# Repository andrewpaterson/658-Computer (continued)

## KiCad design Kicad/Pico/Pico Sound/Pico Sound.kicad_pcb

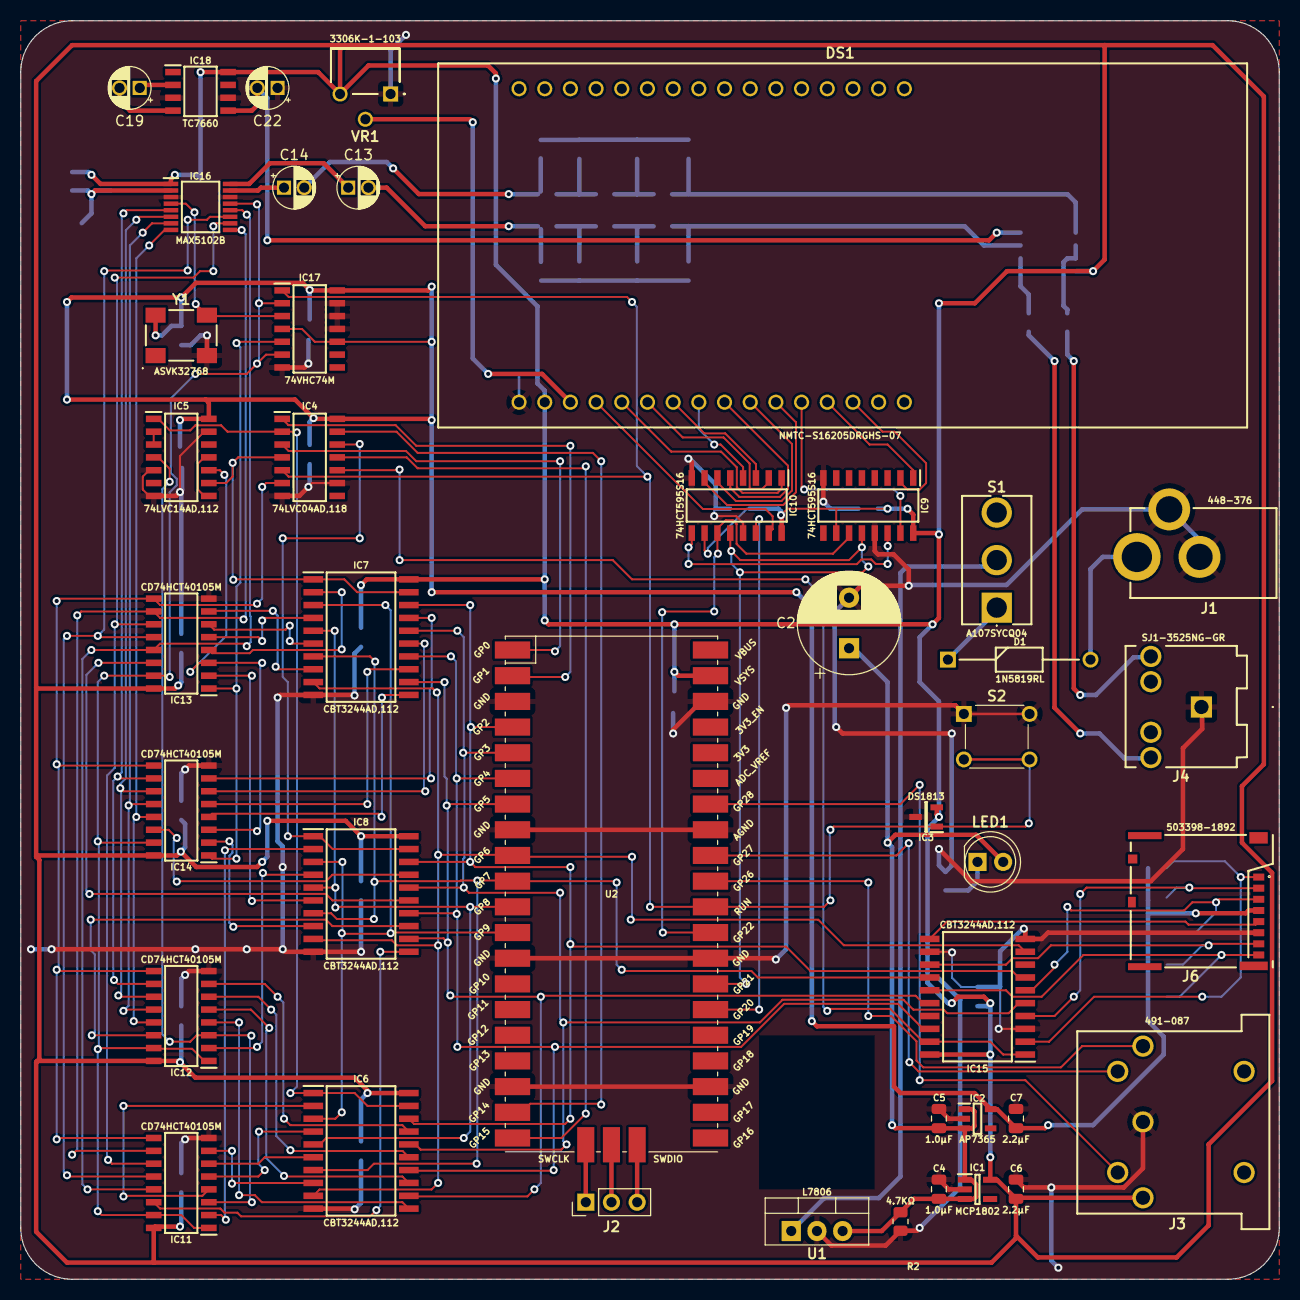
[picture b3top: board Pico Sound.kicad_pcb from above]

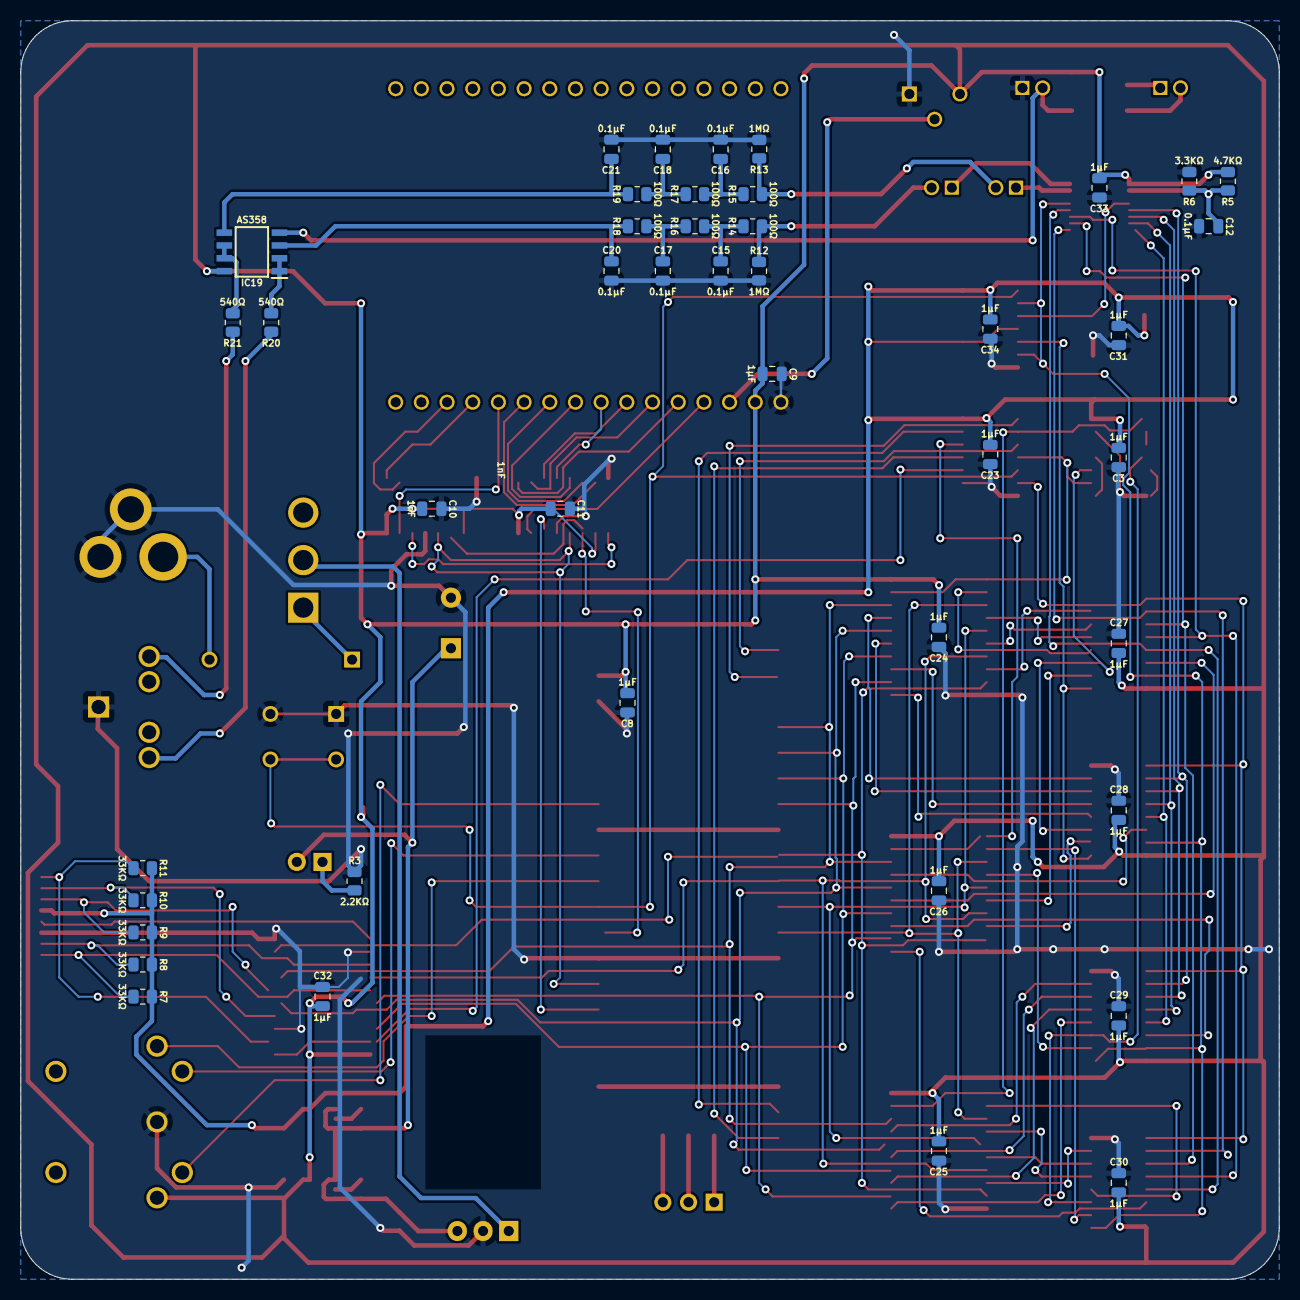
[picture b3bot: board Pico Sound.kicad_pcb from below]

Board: 2 copper layers, 124.5 x 124.5 mm, 85 parts (43 on the bottom side), 111 nets.

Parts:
C2: C_Polarized; CP_Radial_D10.0mm_P5.00mm
C3, C4, C5, C6, C7, C8, C9, C10, C11, C12, C15, C16, C17, C18, C20, C21, C23, C24, C25, C26, C27, C28, C29, C30, C31, C32, C33, C34: C_0805
C13, C14, C19, C22: C_Polarized; CP_Radial_D4.0mm_P2.00mm
D1: 1N5819RL; DIOAD1414W86L464D238
DS1: NMTC-S16205DRGHS-07; NMTCS16205DRGHS07_1
IC1: MCP1802T-5002I_OT; SOT95P270X145-5N
IC2: AP7365-33WG-7; SOT95P285X130-5N
IC3: DS1813R-10+T&R; SOT95P237X112-3N
IC4: 74LVC04AD,118; SOIC127P600X175-14N
IC5: 74LVC14AD,112; SOIC127P600X175-14N
IC6, IC7, IC8, IC15: CBT3244AD,112; SOIC127P1032X265-20N
IC9, IC10: 74HCT595S16; SOIC127P600X175-16N
IC11, IC12, IC13, IC14: CD74HCT40105M; SOIC127P600X175-16N
IC16: MAX5102BEUE+T; SOP65P640X110-16N
IC17: 74VHC74M; SOIC127P600X175-14N
IC18: TC7660EOA; SOIC127P600X175-8N
IC19: AS358AMTR-G1; SOIC127P600X175-8N
J1: 448-376; 448376
J2: Conn_01x03_Male; PinHeader_1x03_P2.54mm_Vertical
J3: 491-087; 491087
J4: SJ1-3525NG-GR; SJ13525NGGR
J6: 503398-1892
LED1: LED; LED_D5.0mm
R2, R3, R5, R6, R7, R8, R9, R10, R11, R12, R13, R14, R15, R16, R17, R18, R19, R20, R21: R_0805
S1: A107SYCQ04
S2: DTS-62N-V; DTS62NV
U1: L7806; TO-220-3_Vertical
U2: Pico; RPi_Pico_SMD
VR1: 3306K-1-103; 3306K1103
Y1: ASVK-32.768KHZ-LJT; ASVK32768KHZLJT

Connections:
/3.3V: C3.1, C7.1, C23.1, C31.1, C34.1, IC2.5 (VOUT), IC4.14 (3V), IC5.14 (3V), IC17.4 (~PR1), IC17.10 (~PR2), IC17.14 (5V), J6.4 (VDD), R7.2, R8.2, R9.2, R10.2, R11.2, Y1.4 (3V)
/5V: C6.1, C8.1, C9.1, C10.1, C11.1, C24.1, C25.1, C26.1, C27.1, C28.1, C29.1, C30.1, C32.1, C33.1, DS1.2 (5V), IC1.5 (VOUT), IC3.2 (5V), IC6.20 (5V), IC7.20 (5V), IC8.20 (5V), IC9.10 (~MR), IC9.16 (VCC), IC10.10 (~MR), IC10.16 (VCC), IC11.16 (5V), IC12.16 (5V), IC13.16 (5V), IC14.16 (5V), IC15.20 (5V), IC16.1 (VDD), IC18.8 (V+), IC19.8 (VCC), J3.3, R5.1, U2.39 (VSYS), VR1.3 (VIN)
/6V: C2.1, C4.1, C5.1, IC1.1 (VIN), IC1.3 (~SHDN), IC2.1 (VIN), IC2.3 (EN), LED1.2 (A), R2.1, U1.3 (OUT)
/16KHz CLK: IC13.1 (~EN(TSC)), IC14.1 (~EN(TSC)), IC17.5 (Q1)
/32KHz CLK: IC16.4 (~WR), IC17.3 (CK1), Y1.3 (OUTPUT)
/-5V: C22.2, IC18.5 (VOUT), IC19.4 (GND)
/Channel A Load: IC4.2 (1Y), IC5.1 (1A), IC6.1 (1~OE), IC6.19 (2~OE)
/Channel B Load: IC4.4 (2Y), IC5.9 (4A), IC7.1 (1~OE), IC7.19 (2~OE)
/DIOR EN: IC4.12 (6Y), IC8.1 (1~OE), IC8.19 (2~OE)
/DIR1: IC8.2 (1A1), IC11.2 (DIR)
/DIR2: IC8.4 (1A2), IC12.2 (DIR)
/DIR3: IC8.6 (1A3), IC13.2 (DIR)
/DIR4: IC8.8 (1A4), IC14.2 (DIR)
/DOR1: IC8.11 (2A1), IC11.14 (DOR)
/DOR2: IC8.13 (2A2), IC12.14 (DOR)
/DOR3: IC8.15 (2A3), IC13.14 (DOR)
/DOR4: IC8.17 (2A4), IC14.14 (DOR)
/GND: C2.2, C3.2, C4.2, C5.2, C6.2, C7.2, C8.2, C9.2, C10.2, C11.2, C12.1, C15.1, C16.1, C17.1, C18.1, C20.1, C21.1, C22.1, C23.2, C24.2, C25.2, C26.2, C27.2, C28.2, C29.2, C30.2, C31.2, C32.2, C33.2, C34.2, DS1.1 (GND), IC1.2 (VSS), IC2.2 (GND), IC3.3 (GND), IC4.7 (GND), IC4.9 (4A), IC5.5 (3A), IC5.7 (GND), IC5.13 (6A), IC6.10 (GND), IC7.10 (GND), IC8.10 (GND), IC9.8 (GND), IC9.13 (~OE), IC10.8 (GND), IC10.13 (~OE), IC11.8 (GND), IC12.8 (GND), IC13.8 (GND), IC14.8 (GND), IC15.3 (2B4), IC15.10 (GND), IC15.12 (1B4), IC16.3 (SHDN), IC16.14 (GND), IC17.7 (GND), IC17.11 (CK2), IC17.12 (D2), IC17.13 (~CLR2), IC18.3 (GND), IC18.6 (LV), J1.B1 (GND), J1.C1 (GND), J3.2, J4.1 (GND), J6.6 (VSS), R2.2, R3.2, R6.1, R12.1, R13.1, S2.1 (C1), S2.2 (C2), U1.2 (GND), U2.3 (GND), U2.8 (GND), U2.13 (GND), U2.18 (GND), U2.23 (GND), U2.28 (GND), U2.33 (AGND), U2.38 (GND), VR1.1 (GND), Y1.2 (GND)
/GPIO2: IC6.18 (1B1), IC7.18 (1B1), IC8.18 (1B1), IC15.7 (2B2), U2.4 (GPIO2)
/GPIO3: IC6.16 (1B2), IC7.16 (1B2), IC8.16 (1B2), IC15.5 (2B3), U2.5 (GPIO3)
/GPIO4: IC6.14 (1B3), IC7.14 (1B3), IC8.14 (1B3), IC15.18 (1B1), U2.6 (GPIO4)
/GPIO5: IC6.12 (1B4), IC7.12 (1B4), IC8.12 (1B4), IC15.16 (1B2), U2.7 (GPIO5)
/GPIO6: IC6.9 (2B1), IC7.9 (2B1), IC8.9 (2B1), IC15.9 (2B1), U2.9 (GPIO6)
/GPIO7: IC6.7 (2B2), IC7.7 (2B2), IC8.7 (2B2), IC15.14 (1B3), U2.10 (GPIO7)
/GPIO8: IC6.5 (2B3), IC7.5 (2B3), IC8.5 (2B3), U2.11 (GPIO8)
/GPIO9: IC6.3 (2B4), IC7.3 (2B4), IC8.3 (2B4), U2.12 (GPIO9)
/Keypad CP: J3.4, U2.32 (GPIO27_ADC1)
/Keypad PL: J3.1, U2.31 (GPIO26_ADC0)
/Keypad Q_{IN}: J3.5, U2.34 (GPIO28_ADC2)
/LCD Bit Out: IC10.14 (DS), U2.26 (GPIO20)
/LCD DB0: DS1.7 (DB0), IC10.3 (Q3)
/LCD DB1: DS1.8 (DB1), IC10.4 (Q4)
/LCD DB2: DS1.9 (DB2), IC10.5 (Q5)
/LCD DB3: DS1.10 (DB3), IC10.6 (Q6)
/LCD DB4: DS1.11 (DB4), IC10.7 (Q7)
/LCD DB5: DS1.12 (DB5), IC9.15 (Q0)
/LCD DB6: DS1.13 (DB6), IC9.1 (Q1)
/LCD DB7: DS1.14 (DB7), IC9.2 (Q2)
/LCD E: DS1.6 (E), IC10.2 (Q2)
/LCD RS: DS1.4 (RS), IC10.15 (Q0)
/LCD R~W: DS1.5 (R/~W), IC10.1 (Q1)
/LCD Shift Clock: IC9.11 (SHCP), IC10.11 (SHCP), U2.29 (GPIO22)
/LCD Store Clock: IC9.12 (STCP), IC10.12 (STCP), U2.27 (GPIO21)
/Line Out Left: J4.3 (L), R20.2
/Line Out Right: J4.2 (R), R21.2
/Q7S: IC9.14 (DS), IC10.9 (Q7S)
/RST: IC4.6 (3Y), IC11.9 (MR), IC12.9 (MR), IC13.9 (MR), IC14.9 (MR)
/SD Card EN: IC4.10 (5Y), IC15.1 (1~OE), IC15.19 (2~OE)
/SD Clk: IC15.11 (2A1), J6.5 (CLK)
/SD Cmd: IC15.6 (1A3), J6.3 (CMD), R9.1
/SD Dat0: IC15.13 (2A2), J6.7 (DAT0), R8.1
/SD Dat1: IC15.15 (2A3), J6.8 (DAT1), R7.1
/SD Dat2: IC15.2 (1A1), J6.1 (DAT2), R11.1
/SD Dat3: IC15.4 (1A2), J6.2 (CD/DAT3), R10.1
/Socket VCC: D1.2, J1.A1 (VCC)
/VCC: S1.2 (CM), U1.1 (IN)
/V_{0}: DS1.3 (V_{O}), VR1.2 (VOUT)
/~16KHz CLK: IC11.1 (~EN(TSC)), IC11.15 (~SO), IC12.1 (~EN(TSC)), IC12.15 (~SO), IC13.15 (~SO), IC14.15 (~SO), IC16.13 (A0), IC17.2 (D1), IC17.6 (~Q1)
/~RST: IC3.1 (~RST), IC4.5 (3A), IC17.1 (~CLR1), S2.3 (N1), S2.4 (N2), U2.30 (RUN)
unnamed: C13.2, R12.2, R14.1
unnamed: C14.2, R13.2, R15.1
unnamed: C15.2, R14.2, R16.1
unnamed: C16.2, R15.2, R17.1
unnamed: C17.2, R16.2, R18.1
unnamed: C18.2, R17.2, R19.1
unnamed: IC4.1 (1A), U2.2 (GPIO1)
unnamed: IC4.3 (2A), U2.1 (GPIO0)
unnamed: IC4.11 (5A), U2.20 (GPIO15)
unnamed: IC4.13 (6A), U2.19 (GPIO14)
unnamed: IC5.2 (1Y), IC5.3 (2A)
unnamed: IC5.8 (4Y), IC5.11 (5A)
unnamed: IC6.2 (1A1), IC11.4 (D0)
unnamed: IC6.4 (1A2), IC11.5 (D1)
unnamed: IC6.6 (1A3), IC11.6 (D2)
unnamed: IC6.8 (1A4), IC11.7 (D3)
unnamed: IC11.13 (Q0), IC13.13 (Q0), IC16.12 (D0)
unnamed: IC11.12 (Q1), IC13.12 (Q1), IC16.11 (D1)
unnamed: IC11.11 (Q2), IC13.11 (Q2), IC16.10 (D2)
unnamed: IC11.10 (Q3), IC13.10 (Q3), IC16.9 (D3)
unnamed: IC5.4 (2Y), IC11.3 (SI), IC12.3 (SI)
unnamed: IC6.11 (2A1), IC12.4 (D0)
unnamed: IC6.13 (2A2), IC12.5 (D1)
unnamed: IC6.15 (2A3), IC12.6 (D2)
unnamed: IC6.17 (2A4), IC12.7 (D3)
unnamed: IC12.13 (Q0), IC14.13 (Q0), IC16.8 (D4)
unnamed: IC12.12 (Q1), IC14.12 (Q1), IC16.7 (D5)
unnamed: IC12.11 (Q2), IC14.11 (Q2), IC16.6 (D6)
unnamed: IC12.10 (Q3), IC14.10 (Q3), IC16.5 (D7)
unnamed: IC7.2 (1A1), IC13.4 (D0)
unnamed: IC7.4 (1A2), IC13.5 (D1)
unnamed: IC7.6 (1A3), IC13.6 (D2)
unnamed: IC7.8 (1A4), IC13.7 (D3)
unnamed: IC5.10 (5Y), IC13.3 (SI), IC14.3 (SI)
unnamed: IC7.11 (2A1), IC14.4 (D0)
unnamed: IC7.13 (2A2), IC14.5 (D1)
unnamed: IC7.15 (2A3), IC14.6 (D2)
unnamed: IC7.17 (2A4), IC14.7 (D3)
unnamed: C13.1, IC16.16 (OUTA)
unnamed: C14.1, IC16.15 (OUTB)
unnamed: C12.2, IC16.2 (REF), R5.2, R6.2
unnamed: C19.1, IC18.2 (CAP+)
unnamed: C19.2, IC18.4 (CAP-)
unnamed: C20.2, IC19.3 (IN_1+), R18.2
unnamed: IC19.1 (OUT_1), IC19.2 (IN_1-), R20.1
unnamed: C21.2, IC19.5 (IN_2+), R19.2
unnamed: IC19.6 (IN_2-), IC19.7 (OUT_2), R21.1
unnamed: J2.1, U2.41 (SWCLK)
unnamed: J2.2, U2.42 (GND)
unnamed: J2.3, U2.43 (SWDIO)
unnamed: LED1.1 (K), R3.1
unnamed: D1.1, S1.1

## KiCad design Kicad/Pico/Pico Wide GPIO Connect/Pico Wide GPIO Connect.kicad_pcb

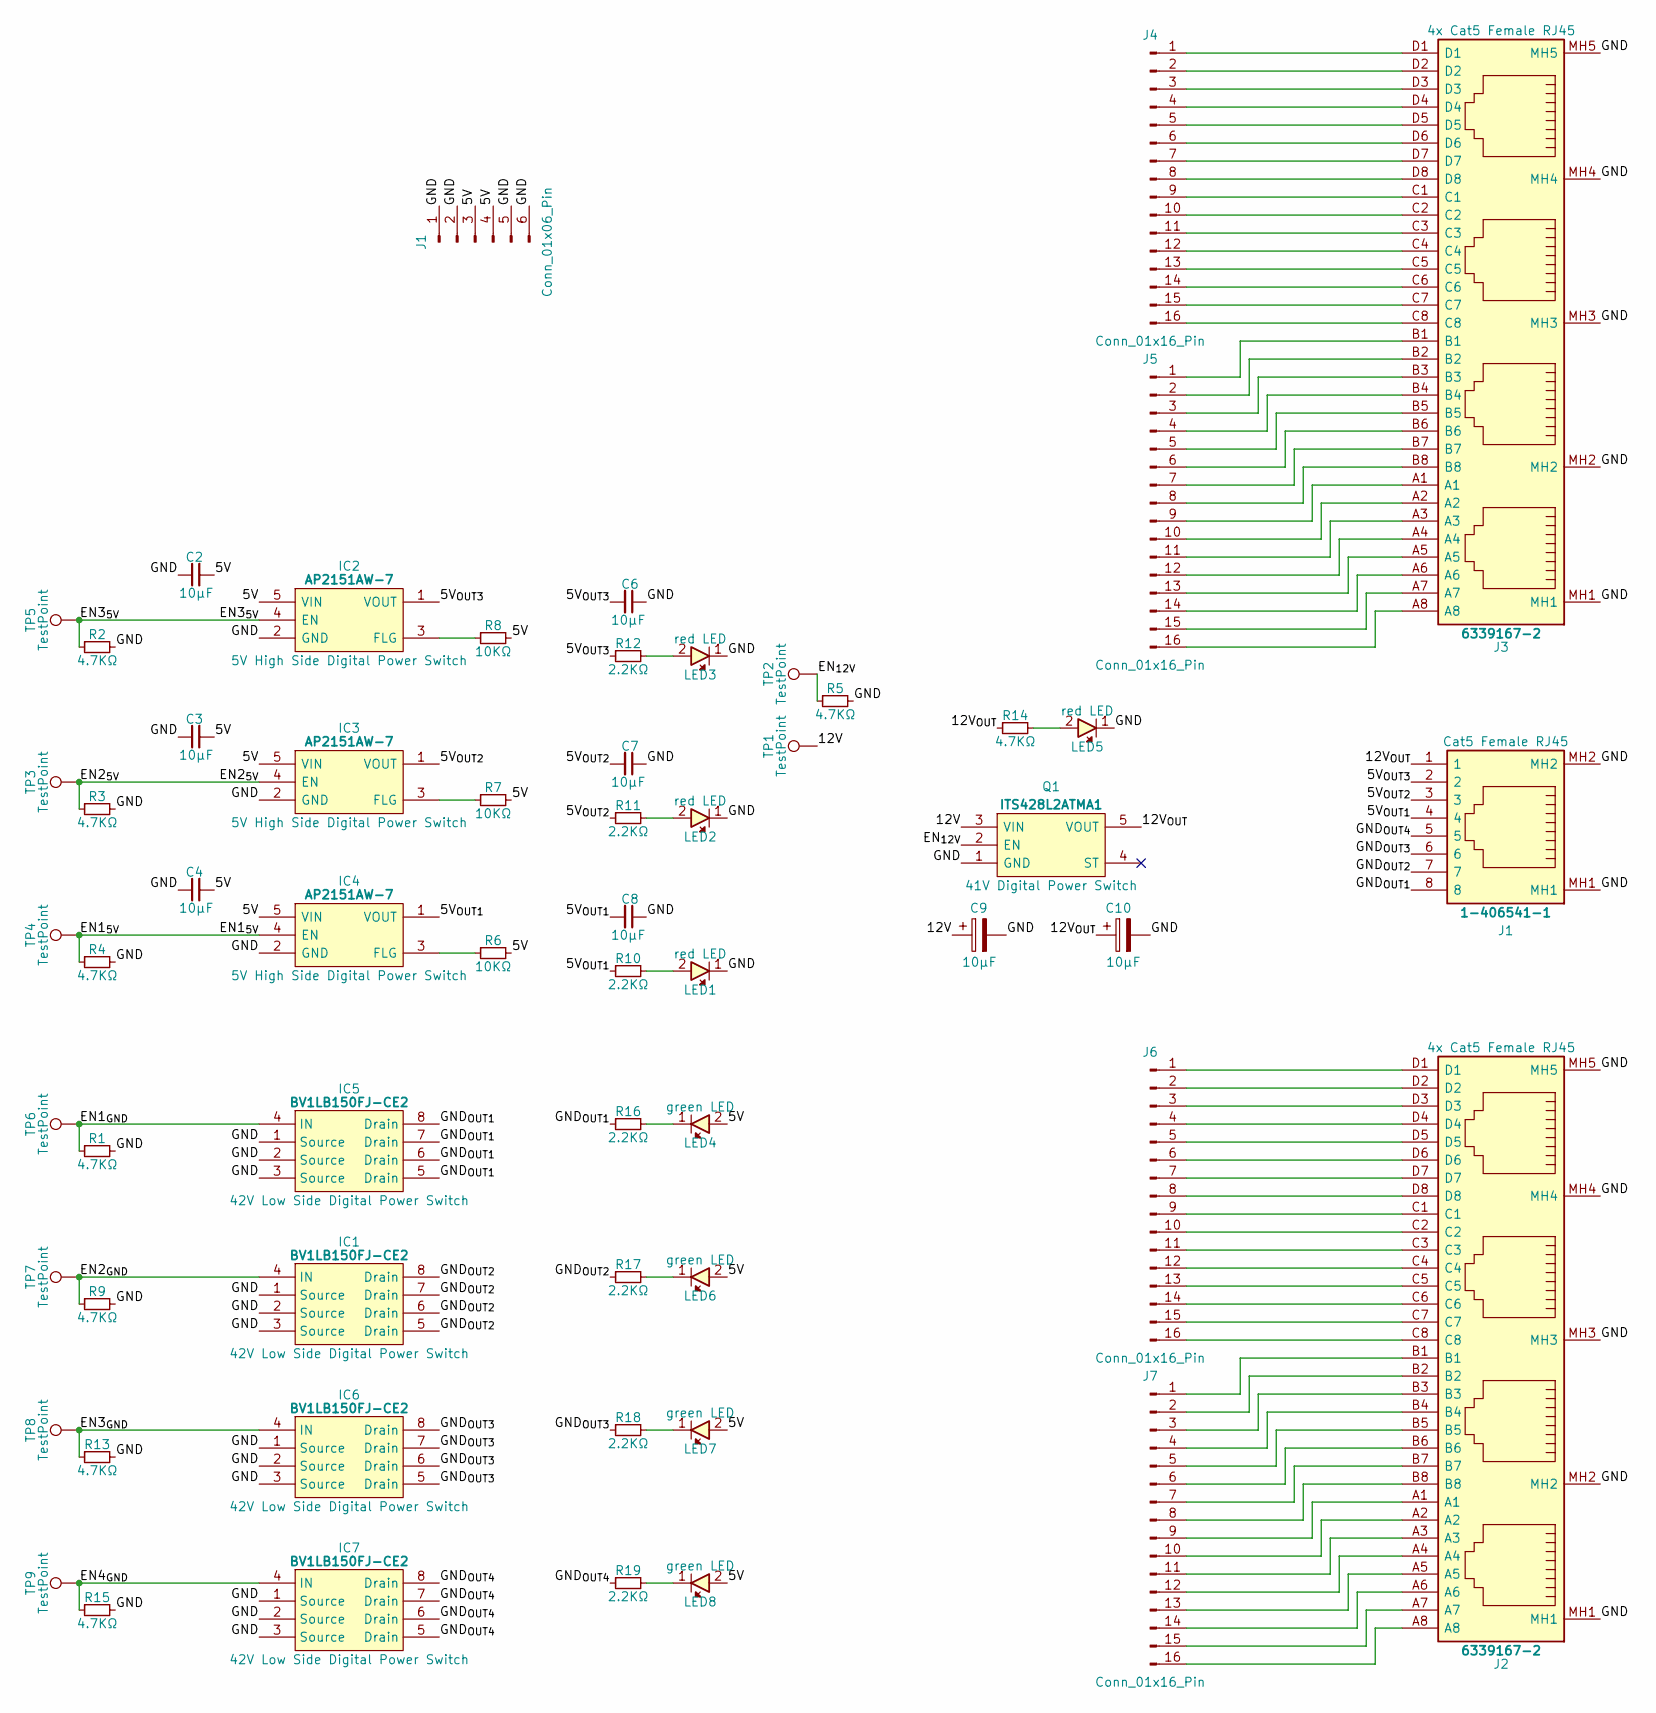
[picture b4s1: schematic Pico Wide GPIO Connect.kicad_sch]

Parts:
C2, C3, C4, C6, C7, C8: 10μF; C_0805
C9, C10: 10μF; CP_Radial_D4.0mm_P2.00mm
IC1, IC5, IC6, IC7: BV1LB150FJ-CE2; SOIC127P600X165-8N; Manufacturer_Part_Number BV1LB150FJ-CE2; Mouser Part Number 755-BV1LB150FJ-CE2
IC2, IC3, IC4: AP2151AW-7; SOT95P285X130-5N; Manufacturer_Part_Number AP2151AW-7; Mouser Part Number 621-AP2151AW-7
J1: 1-406541-1; 1-406541-1_1; Manufacturer_Part_Number 1-406541-1; Mouser Part Number 571-1-406541-1
J2, J3: 6339167-2; 63391672; Manufacturer_Part_Number 6339167-2; Mouser Part Number 571-6339167-2
J4, J5, J6, J7: Conn_01x16_Pin; PinSocket_1x16_P2.54mm_Vertical
LED1, LED2, LED3, LED5: 150224SS73100; 150224SS73100A; Manufacturer_Part_Number 150224SS73100; Mouser Part Number 710-150224SS73100
LED4, LED6, LED7, LED8: 150224VS73100A; Manufacturer_Part_Number 150224VS73100A; Mouser Part Number 710-150224VS73100A
Q1: ITS428L2ATMA1; Manufacturer_Part_Number ITS428L2ATMA1; Mouser Part Number 726-ITS428L2ATMA1
R1, R2, R3, R4, R5, R9, R13, R14, R15: 4.7KΩ; R_0805
R6, R7, R8: 10KΩ; R_0805
R10, R11, R12, R16, R17, R18, R19: 2.2KΩ; R_0805
TP1: TestPoint; TestPoint_Pad_2.5x2.5mm
TP2, TP3, TP4, TP5, TP6, TP7, TP8, TP9: TestPoint; TestPoint_Pad_1.5x1.5mm

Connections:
/12V: C9.1, Q1.3 (VIN), TP1.1
/EN1_{5V}: IC4.4 (EN), R4.1, TP4.1
/EN1_{GND}: IC5.4 (IN), R1.1, TP6.1
/EN2_{5V}: IC3.4 (EN), R3.1, TP3.1
/EN2_{GND}: IC1.4 (IN), R9.1, TP7.1
/EN3_{5V}: IC2.4 (EN), R2.1, TP5.1
/EN3_{GND}: IC6.4 (IN), R13.1, TP8.1
/EN4_{GND}: IC7.4 (IN), R15.1, TP9.1
/EN_{12V}: Q1.2 (EN), R5.1, TP2.1
/GND_{OUT1}: IC5.5 (Drain), IC5.6 (Drain), IC5.7 (Drain), IC5.8 (Drain), J1.8, R16.1
/GND_{OUT2}: IC1.5 (Drain), IC1.6 (Drain), IC1.7 (Drain), IC1.8 (Drain), J1.7, R17.1
unnamed: IC2.3 (FLG), R8.1
unnamed: IC3.3 (FLG), R7.1
unnamed: IC4.3 (FLG), R6.1
unnamed: J3.D1, J4.1
unnamed: J3.D2, J4.2
unnamed: J3.D3, J4.3
unnamed: J3.D4, J4.4
unnamed: J3.D5, J4.5
unnamed: J3.D6, J4.6
unnamed: J3.D7, J4.7
unnamed: J3.D8, J4.8
unnamed: J3.C1, J4.9
unnamed: J3.C2, J4.10
unnamed: J3.C3, J4.11
unnamed: J3.C4, J4.12
unnamed: J3.C5, J4.13
unnamed: J3.C6, J4.14
unnamed: J3.C7, J4.15
unnamed: J3.C8, J4.16
unnamed: J3.B1, J5.1
unnamed: J3.B2, J5.2
unnamed: J3.B3, J5.3
unnamed: J3.B4, J5.4
unnamed: J3.B5, J5.5
unnamed: J3.B6, J5.6
unnamed: J3.B7, J5.7
unnamed: J3.B8, J5.8
unnamed: J3.A1, J5.9
unnamed: J3.A2, J5.10
unnamed: J3.A3, J5.11
unnamed: J3.A4, J5.12
unnamed: J3.A5, J5.13
unnamed: J3.A6, J5.14
unnamed: J3.A7, J5.15
unnamed: J3.A8, J5.16
unnamed: J2.D1, J6.1
unnamed: J2.D2, J6.2
unnamed: J2.D3, J6.3
unnamed: J2.D4, J6.4
unnamed: J2.D5, J6.5
unnamed: J2.D6, J6.6
unnamed: J2.D7, J6.7
unnamed: J2.D8, J6.8
unnamed: J2.C1, J6.9
unnamed: J2.C2, J6.10
unnamed: J2.C3, J6.11
unnamed: J2.C4, J6.12
unnamed: J2.C5, J6.13
unnamed: J2.C6, J6.14
unnamed: J2.C7, J6.15
unnamed: J2.C8, J6.16
unnamed: J2.B1, J7.1
unnamed: J2.B2, J7.2
unnamed: J2.B3, J7.3
unnamed: J2.B4, J7.4
unnamed: J2.B5, J7.5
unnamed: J2.B6, J7.6
unnamed: J2.B7, J7.7
unnamed: J2.B8, J7.8
unnamed: J2.A1, J7.9
unnamed: J2.A2, J7.10
unnamed: J2.A3, J7.11
unnamed: J2.A4, J7.12
unnamed: J2.A5, J7.13
unnamed: J2.A6, J7.14
unnamed: J2.A7, J7.15
unnamed: J2.A8, J7.16
unnamed: LED1.2, R10.2
unnamed: LED2.2, R11.2
unnamed: LED3.2, R12.2
unnamed: LED4.1, R16.2
unnamed: LED5.2, R14.2
unnamed: LED6.1, R17.2
unnamed: LED7.1, R18.2
unnamed: LED8.1, R19.2

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
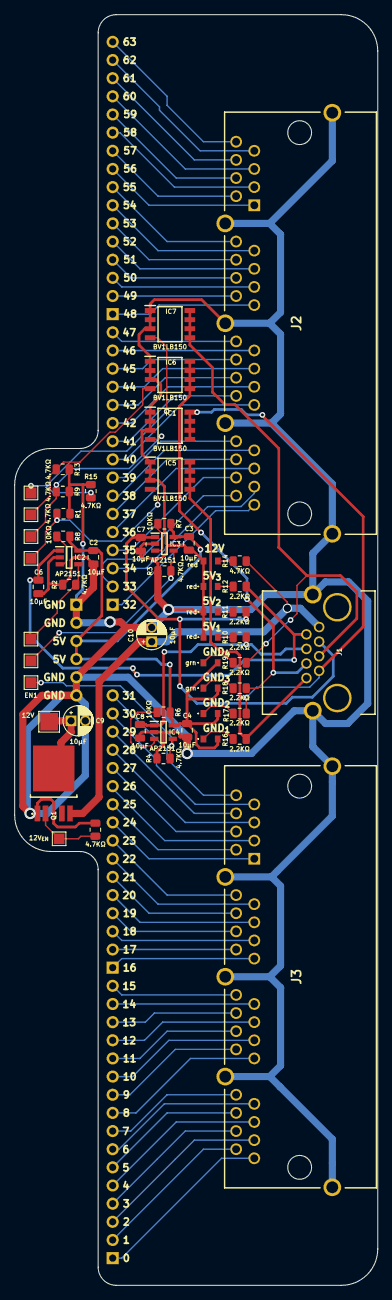
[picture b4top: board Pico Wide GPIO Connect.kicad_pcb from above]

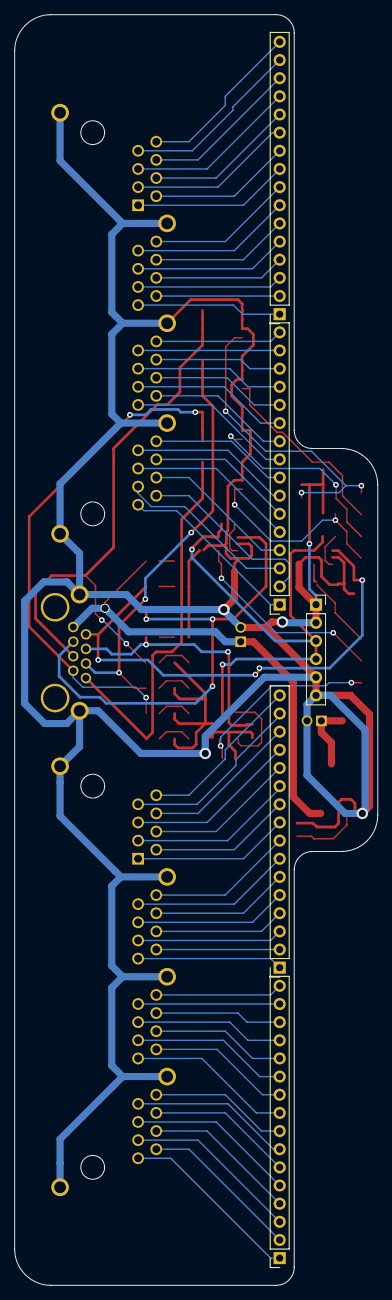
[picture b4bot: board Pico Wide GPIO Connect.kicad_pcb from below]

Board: 2 copper layers, 50.8 x 177.8 mm, 60 parts (5 on the bottom side), 94 nets.

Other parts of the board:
J9: Conn_01x06_Pin; PinSocket_1x06_P2.54mm_Vertical

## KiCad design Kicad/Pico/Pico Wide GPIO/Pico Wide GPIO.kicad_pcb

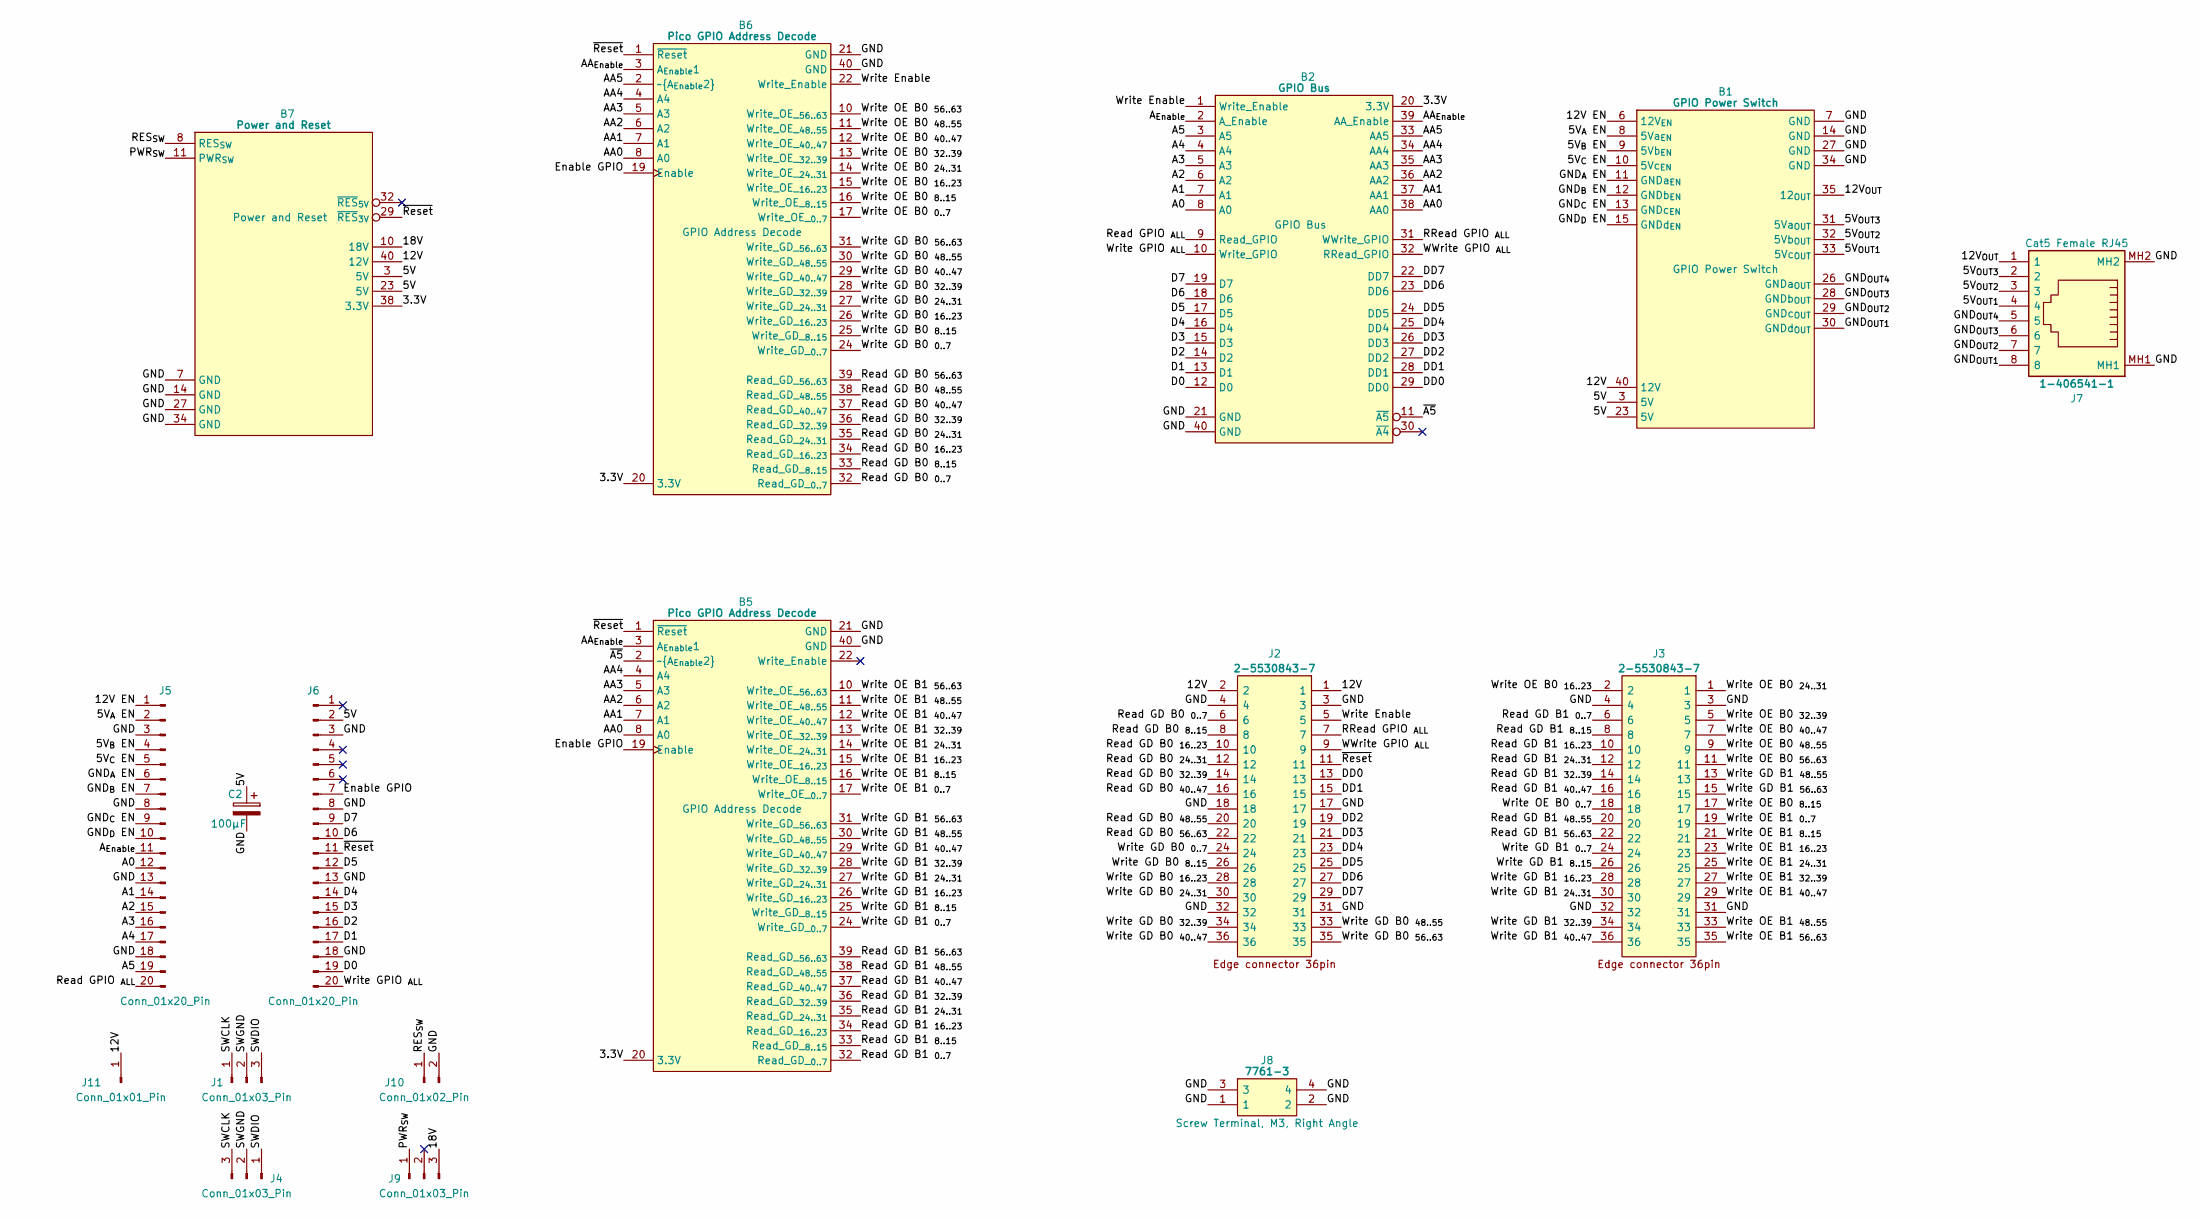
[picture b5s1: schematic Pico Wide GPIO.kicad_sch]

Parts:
B1: GPIO Power Switch; HCP65_GPIO_Power_Switch
B2: GPIO Bus; HCP65_GPIO_Bus
B5, B6: Pico GPIO Address Decode; HCP65_GPIO_Address_Decode
B7: Power and Reset; HCP65_Power_and_Reset
C2: 100μF; CP_Radial_D6.3mm_P2.50mm
J1: Conn_01x03_Pin; PinSocket_1x03_P2.54mm_Vertical
J2, J3: 2-5530843-7; 36pin Edge Connector; Manufacturer_Part_Number 2-5530843-7; Mouser Part Number 571-2-5530843-7
J4: Conn_01x03_Pin; PinHeader_1x03_P2.54mm_Horizontal
J5, J6: Conn_01x20_Pin; PinSocket_1x20_P2.54mm_Vertical
J7: 1-406541-1; 1-406541-1_1; Manufacturer_Part_Number 1-406541-1; Mouser Part Number 571-1-406541-1
J8: 7761-3; 77613; Manufacturer_Part_Number 7761-3
J9: Conn_01x03_Pin; PinHeader_1x03_P2.54mm_Vertical
J10: Conn_01x02_Pin; PinHeader_1x02_P2.54mm_Vertical
J11: Conn_01x01_Pin; PinSocket_1x01_P2.54mm_Vertical

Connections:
/3.3V: B2.20 (3.3V), B5.20 (3.3V), B6.20 (3.3V), B7.38 (3.3V)
/5V: B1.3 (5V), B1.23 (5V), B7.3 (5V), B7.23 (5V), C2.1, J6.2
/5V_{A} EN: B1.8 (5Va_{EN}), J5.2
/5V_{B} EN: B1.9 (5Vb_{EN}), J5.4
/5V_{C} EN: B1.10 (5Vc_{EN}), J5.5
/5V_{OUT1}: B1.33 (5Vc_{OUT}), J7.4
/5V_{OUT2}: B1.32 (5Vb_{OUT}), J7.3
/5V_{OUT3}: B1.31 (5Va_{OUT}), J7.2
/12V: B1.40 (12V), B7.40 (12V), J2.1, J2.2, J11.1
/12V EN: B1.6 (12V_{EN}), J5.1
/12V_{OUT}: B1.35 (12_{OUT}), J7.1
/18V: B7.10 (18V), J9.3
/A0: B2.8 (A0), J5.12
/A1: B2.7 (A1), J5.14
/A2: B2.6 (A2), J5.15
/A3: B2.5 (A3), J5.16
/A4: B2.4 (A4), J5.17
/A5: B2.3 (A5), J5.19
/AA0: B2.38 (AA0), B5.8 (A0), B6.8 (A0)
/AA1: B2.37 (AA1), B5.7 (A1), B6.7 (A1)
/AA2: B2.36 (AA2), B5.6 (A2), B6.6 (A2)
/AA3: B2.35 (AA3), B5.5 (A3), B6.5 (A3)
/AA4: B2.34 (AA4), B5.4 (A4), B6.4 (A4)
/AA5: B2.33 (AA5), B6.2 (~A_{Enable2})
/AA_{Enable}: B2.39 (AA_Enable), B5.3 (A_{Enable}1), B6.3 (A_{Enable}1)
/A_{Enable}: B2.2 (A_Enable), J5.11
/D0: B2.12 (D0), J6.19
/D1: B2.13 (D1), J6.17
/D2: B2.14 (D2), J6.16
/D3: B2.15 (D3), J6.15
/D4: B2.16 (D4), J6.14
/D5: B2.17 (D5), J6.12
/D6: B2.18 (D6), J6.10
/D7: B2.19 (D7), J6.9
/DD0: B2.29 (DD0), J2.13
/DD1: B2.28 (DD1), J2.15
/DD2: B2.27 (DD2), J2.19
/DD3: B2.26 (DD3), J2.21
/DD4: B2.25 (DD4), J2.23
/DD5: B2.24 (DD5), J2.25
/DD6: B2.23 (DD6), J2.27
/DD7: B2.22 (DD7), J2.29
/Enable GPIO: B5.19 (Enable), B6.19 (Enable), J6.7
/GND: B1.7 (GND), B1.14 (GND), B1.27 (GND), B1.34 (GND), B2.21 (GND), B2.40 (GND), B5.21 (GND), B5.40 (GND), B6.21 (GND), B6.40 (GND), B7.7 (GND), B7.14 (GND), B7.27 (GND), B7.34 (GND), C2.2, J2.3, J2.4, J2.17, J2.18, J2.31, J2.32, J3.3, J3.4, J3.31, J3.32, J5.3, J5.8, J5.13, J5.18, J6.3, J6.8, J6.13, J6.18, J7.MH1, J7.MH2, J8.1, J8.2, J8.3, J8.4, J10.2
/GND_{A} EN: B1.11 (GNDa_{EN}), J5.6
/GND_{B} EN: B1.12 (GNDb_{EN}), J5.7
/GND_{C} EN: B1.13 (GNDc_{EN}), J5.9
/GND_{D} EN: B1.15 (GNDd_{EN}), J5.10
/GND_{OUT1}: B1.30 (GNDd_{OUT}), J7.8
/GND_{OUT2}: B1.29 (GNDc_{OUT}), J7.7
/GND_{OUT3}: B1.28 (GNDb_{OUT}), J7.6
/GND_{OUT4}: B1.26 (GNDa_{OUT}), J7.5
/PWR_{SW}: B7.11 (PWR_{SW}), J9.1
/RES_{SW}: B7.8 (RES_{SW}), J10.1
/RRead GPIO _{ALL}: B2.31 (WWrite_GPIO), J2.7
/Read GD B0 _{0..7}: B6.32 (Read_GD__{0..7}), J2.6
/Read GD B0 _{8..15}: B6.33 (Read_GD__{8..15}), J2.8
/Read GD B0 _{16..23}: B6.34 (Read_GD__{16..23}), J2.10
/Read GD B0 _{24..31}: B6.35 (Read_GD__{24..31}), J2.12
/Read GD B0 _{32..39}: B6.36 (Read_GD__{32..39}), J2.14
/Read GD B0 _{40..47}: B6.37 (Read_GD__{40..47}), J2.16
/Read GD B0 _{48..55}: B6.38 (Read_GD__{48..55}), J2.20
/Read GD B0 _{56..63}: B6.39 (Read_GD__{56..63}), J2.22
/Read GD B1 _{0..7}: B5.32 (Read_GD__{0..7}), J3.6
/Read GD B1 _{8..15}: B5.33 (Read_GD__{8..15}), J3.8
/Read GD B1 _{16..23}: B5.34 (Read_GD__{16..23}), J3.10
/Read GD B1 _{24..31}: B5.35 (Read_GD__{24..31}), J3.12
/Read GD B1 _{32..39}: B5.36 (Read_GD__{32..39}), J3.14
/Read GD B1 _{40..47}: B5.37 (Read_GD__{40..47}), J3.16
/Read GD B1 _{48..55}: B5.38 (Read_GD__{48..55}), J3.20
/Read GD B1 _{56..63}: B5.39 (Read_GD__{56..63}), J3.22
/Read GPIO _{ALL}: B2.9 (Read_GPIO), J5.20
/SWCLK: J1.1, J4.3
/SWDIO: J1.3, J4.1
/SWGND: J1.2, J4.2
/WWrite GPIO _{ALL}: B2.32 (RRead_GPIO), J2.9
/Write Enable: B2.1 (Write_Enable), B6.22 (Write_Enable), J2.5
/Write GD B0 _{0..7}: B6.24 (Write_GD__{0..7}), J2.24
/Write GD B0 _{8..15}: B6.25 (Write_GD__{8..15}), J2.26
/Write GD B0 _{16..23}: B6.26 (Write_GD__{16..23}), J2.28
/Write GD B0 _{24..31}: B6.27 (Write_GD__{24..31}), J2.30
/Write GD B0 _{32..39}: B6.28 (Write_GD__{32..39}), J2.34
/Write GD B0 _{40..47}: B6.29 (Write_GD__{40..47}), J2.36
/Write GD B0 _{48..55}: B6.30 (Write_GD__{48..55}), J2.33
/Write GD B0 _{56..63}: B6.31 (Write_GD__{56..63}), J2.35
/Write GD B1 _{0..7}: B5.24 (Write_GD__{0..7}), J3.24
/Write GD B1 _{8..15}: B5.25 (Write_GD__{8..15}), J3.26
/Write GD B1 _{16..23}: B5.26 (Write_GD__{16..23}), J3.28
/Write GD B1 _{24..31}: B5.27 (Write_GD__{24..31}), J3.30
/Write GD B1 _{32..39}: B5.28 (Write_GD__{32..39}), J3.34
/Write GD B1 _{40..47}: B5.29 (Write_GD__{40..47}), J3.36
/Write GD B1 _{48..55}: B5.30 (Write_GD__{48..55}), J3.13
/Write GD B1 _{56..63}: B5.31 (Write_GD__{56..63}), J3.15
/Write GPIO _{ALL}: B2.10 (Write_GPIO), J6.20
/Write OE B0 _{0..7}: B6.17 (Write_OE__{0..7}), J3.18
/Write OE B0 _{8..15}: B6.16 (Write_OE__{8..15}), J3.17
/Write OE B0 _{16..23}: B6.15 (Write_OE__{16..23}), J3.2
/Write OE B0 _{24..31}: B6.14 (Write_OE__{24..31}), J3.1
/Write OE B0 _{32..39}: B6.13 (Write_OE__{32..39}), J3.5
/Write OE B0 _{40..47}: B6.12 (Write_OE__{40..47}), J3.7
/Write OE B0 _{48..55}: B6.11 (Write_OE__{48..55}), J3.9
/Write OE B0 _{56..63}: B6.10 (Write_OE__{56..63}), J3.11
/Write OE B1 _{0..7}: B5.17 (Write_OE__{0..7}), J3.19
/Write OE B1 _{8..15}: B5.16 (Write_OE__{8..15}), J3.21
/Write OE B1 _{16..23}: B5.15 (Write_OE__{16..23}), J3.23
/Write OE B1 _{24..31}: B5.14 (Write_OE__{24..31}), J3.25
/Write OE B1 _{32..39}: B5.13 (Write_OE__{32..39}), J3.27
/Write OE B1 _{40..47}: B5.12 (Write_OE__{40..47}), J3.29
/Write OE B1 _{48..55}: B5.11 (Write_OE__{48..55}), J3.33
/Write OE B1 _{56..63}: B5.10 (Write_OE__{56..63}), J3.35
/~A5: B2.11 (~A5), B5.2 (~A_{Enable2})
/~Reset: B5.1 (~Reset), B6.1 (~Reset), B7.29 (~RES_{3V}), J2.11, J6.11

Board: 2 copper layers, 17 parts (1 on the bottom side), 112 nets, no tracks yet.
